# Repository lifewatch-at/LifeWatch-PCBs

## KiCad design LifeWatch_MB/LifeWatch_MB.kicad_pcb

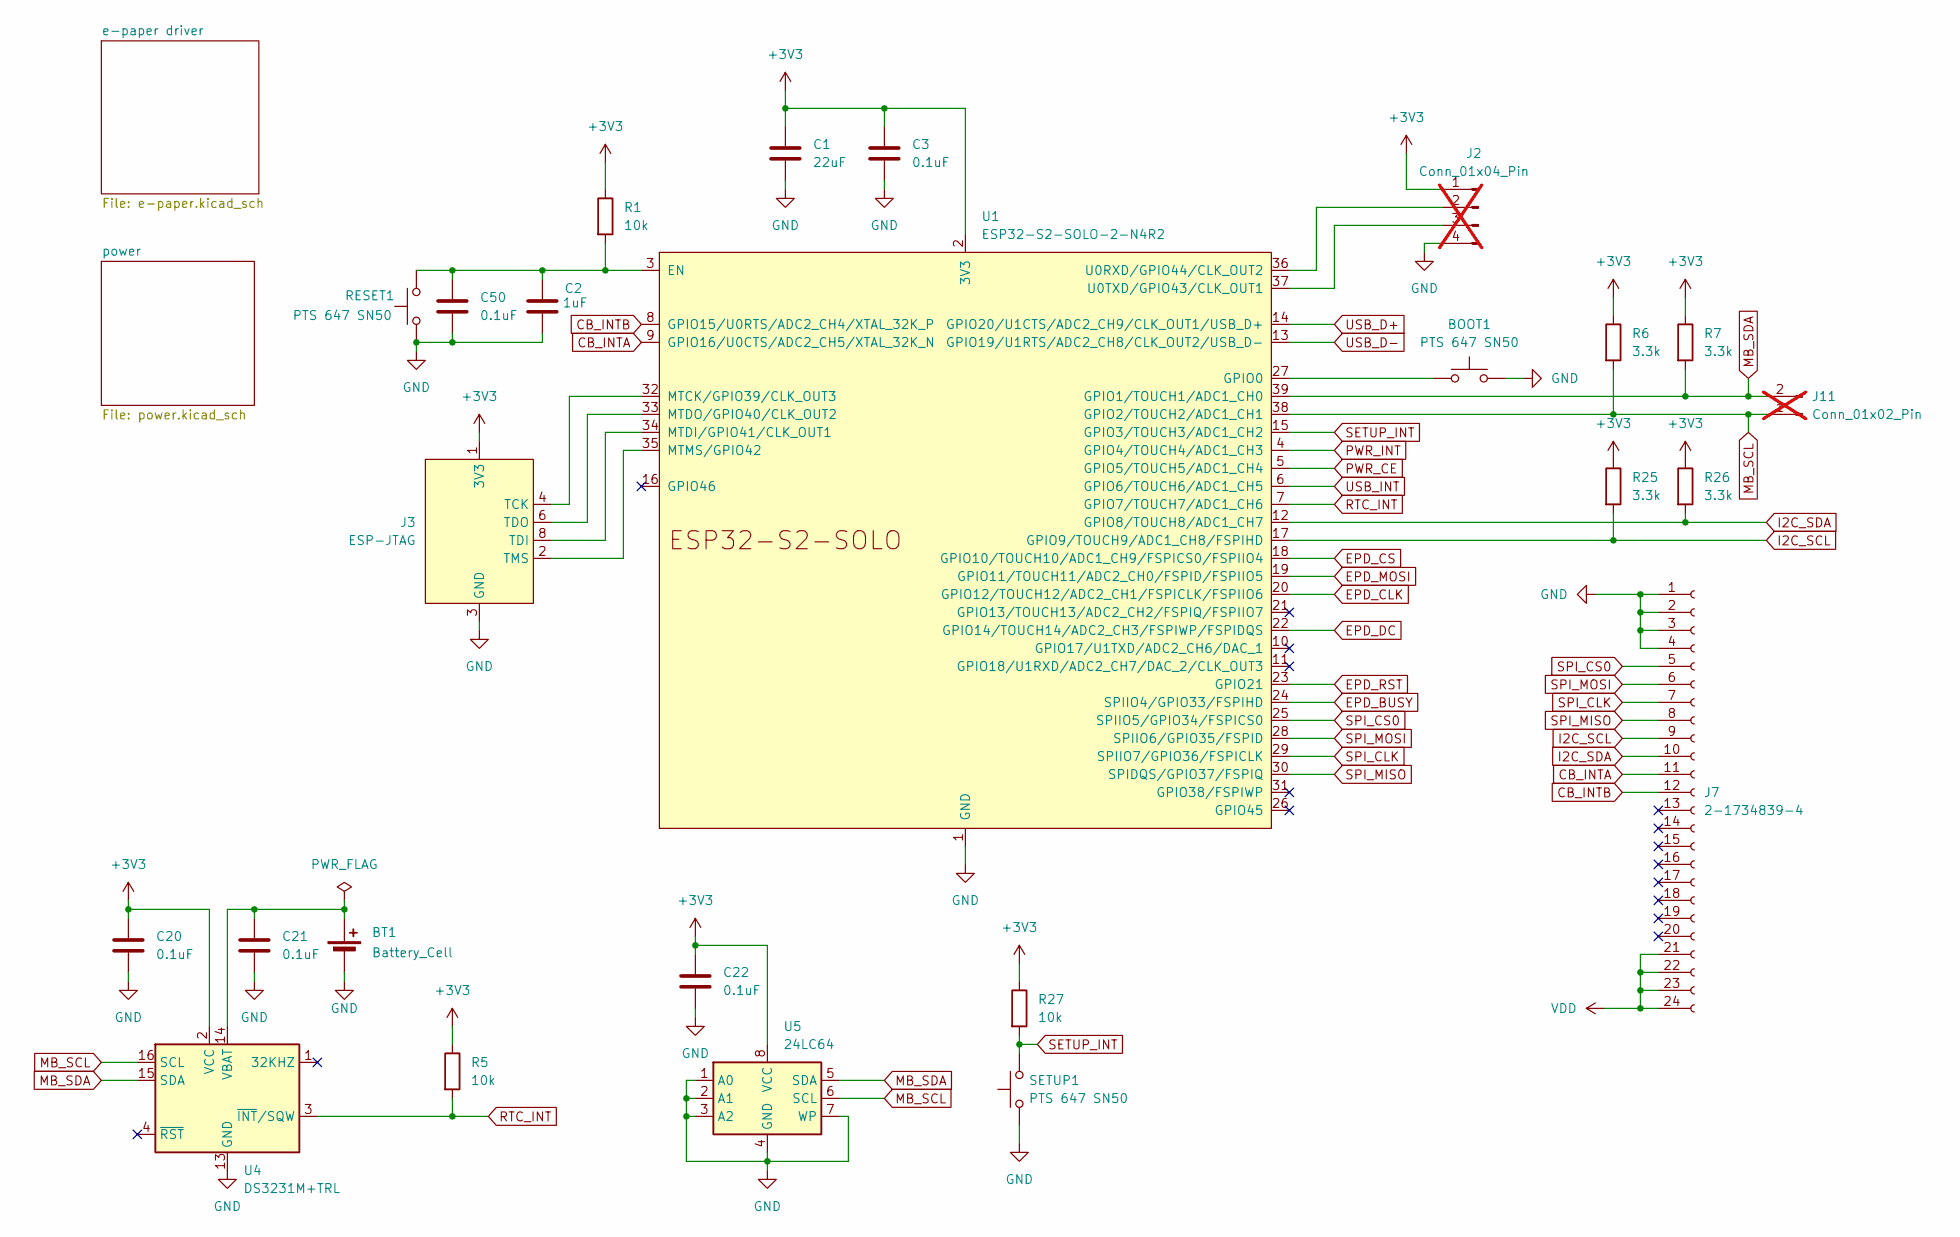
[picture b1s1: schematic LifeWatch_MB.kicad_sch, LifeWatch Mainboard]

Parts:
BOOT1: PTS 647 SN50; SW_SPST_PTS647_Sx50; Manufacturer_Part_Number PTS 647 SN50 SMTR2 LFS
BT1: Battery_Cell; BatteryHolder_Keystone_1060_1x2032; Manufacturer_Part_Number Keystone 3034
C1: 22uF; C_0805_2012Metric; Manufacturer_Part_Number CL21A226MQQNNNE
C2: 1uF; C_0603_1608Metric; Manufacturer_Part_Number CC0603KRX7R7BB105
C3, C20, C21, C22, C50: 0.1uF; C_0402_1005Metric; Manufacturer_Part_Number CL05B104KP5NNNC
J2: Conn_01x04_Pin; PinHeader_1x04_P2.54mm_Vertical; not fitted
J3: ESP-JTAG; IDC-Header_2x05_P2.54mm_Vertical
J7: 2-1734839-4; TE_2-1734839-4_1x24-1MP_P0.5mm_Horizontal; Manufacturer_Part_Number 2-1734839-4
J11: Conn_01x02_Pin; PinHeader_1x02_P2.54mm_Vertical; not fitted
R1, R5, R27: 10k; R_0805_2012Metric; Manufacturer_Part_Number RC0805FR-0710KL
R6, R7, R25, R26: 3.3k; R_0805_2012Metric; Manufacturer_Part_Number RC0805FR-073K3L
RESET1: PTS 647 SN50; SW_SPST_PTS647_Sx50; Manufacturer_Part_Number PTS 647 SN50 SMTR2 LFS
SETUP1: PTS 647 SN50; SW_SPST_PTS647_Sx50; Manufacturer_Part_Number PTS 647 SN50 SMTR2 LFS
U1: ESP32-S2-SOLO-2-N4R2; ESP32-S2-SOLO; Manufacturer_Part_Number ESP32-S2-SOLO-2-N4R2
U4: DS3231M+TRL; SOIC-16W_7.5x10.3mm_P1.27mm; Manufacturer_Part_Number DS3231M+TRL
U5: 24LC64; SOIC-8_3.9x4.9mm_P1.27mm; Manufacturer_Part_Number 24LC64T-I/SN

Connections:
+3V3: C1.1, C3.1, C20.1, C22.1, J2.1, J3.1 (3V3), R1.1, R5.1, R6.1, R7.1, R25.1, R26.1, R27.1, U1.2 (3V3), U4.2 (VCC), U5.8 (VCC); also elsewhere on the board
CB_INTA: J7.11, U1.9 (GPIO16/U0CTS/ADC2_CH5/XTAL_32K_N)
CB_INTB: J7.12, U1.8 (GPIO15/U0RTS/ADC2_CH4/XTAL_32K_P)
EPD_BUSY: U1.24 (SPIIO4/GPIO33/FSPIHD); also elsewhere on the board
EPD_CLK: U1.20 (GPIO12/TOUCH12/ADC2_CH1/FSPICLK/FSPIIO6); also elsewhere on the board
EPD_CS: U1.18 (GPIO10/TOUCH10/ADC1_CH9/FSPICS0/FSPIIO4); also elsewhere on the board
EPD_DC: U1.22 (GPIO14/TOUCH14/ADC2_CH3/FSPIWP/FSPIDQS); also elsewhere on the board
EPD_MOSI: U1.19 (GPIO11/TOUCH11/ADC2_CH0/FSPID/FSPIIO5); also elsewhere on the board
EPD_RST: U1.23 (GPIO21); also elsewhere on the board
GND: BOOT1.2, BT1.2 (-), C1.2, C2.2, C3.2, C20.2, C21.2, C22.2, C50.2, J2.4, J3.3 (GND), J3.5 (GND), J3.7 (GND), J3.9 (GND), J7.1, J7.2, J7.3, J7.4, RESET1.1, SETUP1.1, U1.1 (GND), U1.40 (GND), U1.41 (GND), U4.5 (GND), U4.6 (GND), U4.7 (GND), U4.8 (GND), U4.9 (GND), U4.10 (GND), U4.11 (GND), U4.12 (GND), U4.13 (GND), U5.1 (A0), U5.2 (A1), U5.3 (A2), U5.4 (GND), U5.7 (WP); also elsewhere on the board
I2C_SCL: J7.9, R25.2, U1.17 (GPIO9/TOUCH9/ADC1_CH8/FSPIHD)
I2C_SDA: J7.10, R26.2, U1.12 (GPIO8/TOUCH8/ADC1_CH7)
MB_SCL: J11.1, R6.2, U1.38 (GPIO2/TOUCH2/ADC1_CH1), U4.16 (SCL), U5.6 (SCL); also elsewhere on the board
MB_SDA: J11.2, R7.2, U1.39 (GPIO1/TOUCH1/ADC1_CH0), U4.15 (SDA), U5.5 (SDA); also elsewhere on the board
unnamed: BT1.1 (+), C21.1, U4.14 (VBAT)
unnamed: J2.2, U1.36 (U0RXD/GPIO44/CLK_OUT2)
unnamed: J2.3, U1.37 (U0TXD/GPIO43/CLK_OUT1)
unnamed: J3.4 (TCK), U1.32 (MTCK/GPIO39/CLK_OUT3)
unnamed: J3.8 (TDI), U1.34 (MTDI/GPIO41/CLK_OUT1)
unnamed: J3.6 (TDO), U1.33 (MTDO/GPIO40/CLK_OUT2)
unnamed: J3.2 (TMS), U1.35 (MTMS/GPIO42)
unnamed: C2.1, C50.1, R1.2, RESET1.2, U1.3 (EN)
unnamed: BOOT1.1, U1.27 (GPIO0)
PWR_CE: U1.5 (GPIO5/TOUCH5/ADC1_CH4); also elsewhere on the board
PWR_INT: U1.4 (GPIO4/TOUCH4/ADC1_CH3); also elsewhere on the board
RTC_INT: R5.2, U1.7 (GPIO7/TOUCH7/ADC1_CH6), U4.3 (~INT/SQW)
SETUP_INT: R27.2, SETUP1.2, U1.15 (GPIO3/TOUCH3/ADC1_CH2)
SPI_CLK: J7.7, U1.29 (SPIIO7/GPIO36/FSPICLK)
SPI_CS0: J7.5, U1.25 (SPIIO5/GPIO34/FSPICS0)
SPI_MISO: J7.8, U1.30 (SPIDQS/GPIO37/FSPIQ)
SPI_MOSI: J7.6, U1.28 (SPIIO6/GPIO35/FSPID)
USB_D+: U1.14 (GPIO20/U1CTS/ADC2_CH9/CLK_OUT1/USB_D+); also elsewhere on the board
USB_D-: U1.13 (GPIO19/U1RTS/ADC2_CH8/CLK_OUT2/USB_D-); also elsewhere on the board
USB_INT: U1.6 (GPIO6/TOUCH6/ADC1_CH5); also elsewhere on the board
VDD: J7.21, J7.22, J7.23, J7.24; also elsewhere on the board

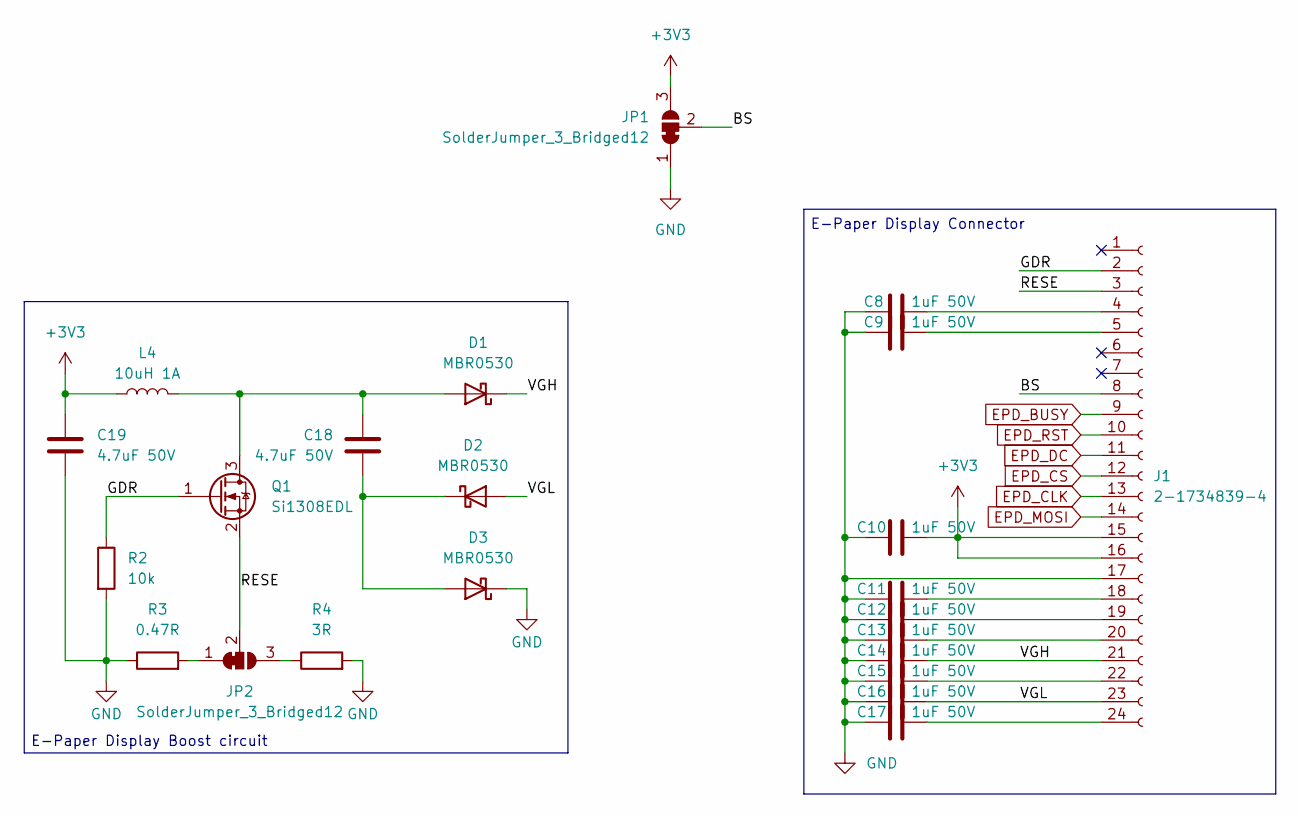
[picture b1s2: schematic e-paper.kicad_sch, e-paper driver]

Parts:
C8, C9, C10, C11, C12, C13, C14, C15, C16, C17: 1uF 50V; C_0805_2012Metric; Manufacturer_Part_Number CL21B105KBFNNNE
C18, C19: 4.7uF 50V; C_0805_2012Metric; Manufacturer_Part_Number GRM21BR61H475KE51L
D1, D2, D3: MBR0530; D_SOD-123; Manufacturer_Part_Number MBR0530T1G
J1: 2-1734839-4; TE_2-1734839-4_1x24-1MP_P0.5mm_Horizontal; Manufacturer_Part_Number 2-1734839-4
JP1, JP2: SolderJumper_3_Bridged12; SolderJumper-3_P1.3mm_Bridged12_RoundedPad1.0x1.5mm
L4: 10uH 1A; L_Vishay_IHLP-2525; Manufacturer_Part_Number IHLP2525CZER100M01
Q1: Si1308EDL; SOT-323_SC-70; Manufacturer_Part_Number SI1308EDL-T1-GE3
R2: 10k; R_0805_2012Metric; Manufacturer_Part_Number RC0805FR-0710KL
R3: 0.47R; R_0805_2012Metric; Manufacturer_Part_Number ERJ-6RQFR47V
R4: 3R; R_0805_2012Metric; Manufacturer_Part_Number RC0805FR-073RL

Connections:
+3V3: C10.2, C19.1, J1.15, J1.16, JP1.3 (B), L4.1; also elsewhere on the board
/e-paper driver/BS: J1.8, JP1.2 (C)
/e-paper driver/GDR: J1.2, Q1.1 (G), R2.1
/e-paper driver/RESE: J1.3, JP2.2 (C), Q1.2 (S)
/e-paper driver/VGH: C14.2, D1.1 (K), J1.21
/e-paper driver/VGL: C16.2, D2.2 (A), J1.23
EPD_BUSY: J1.9; also elsewhere on the board
EPD_CLK: J1.13; also elsewhere on the board
EPD_CS: J1.12; also elsewhere on the board
EPD_DC: J1.11; also elsewhere on the board
EPD_MOSI: J1.14; also elsewhere on the board
EPD_RST: J1.10; also elsewhere on the board
GND: C8.1, C9.1, C10.1, C11.1, C12.1, C13.1, C14.1, C15.1, C16.1, C17.1, C19.2, D3.1 (K), J1.17, JP1.1 (A), R2.2, R3.1, R4.2; also elsewhere on the board
unnamed: C18.1, D1.2 (A), L4.2, Q1.3 (D)
unnamed: C18.2, D2.1 (K), D3.2 (A)
unnamed: C8.2, J1.4
unnamed: C9.2, J1.5
unnamed: C11.2, J1.18
unnamed: C12.2, J1.19
unnamed: C13.2, J1.20
unnamed: C15.2, J1.22
unnamed: C17.2, J1.24
unnamed: JP2.1 (A), R3.2
unnamed: JP2.3 (B), R4.1

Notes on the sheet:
E-Paper Display Connector
E-Paper Display Boost circuit

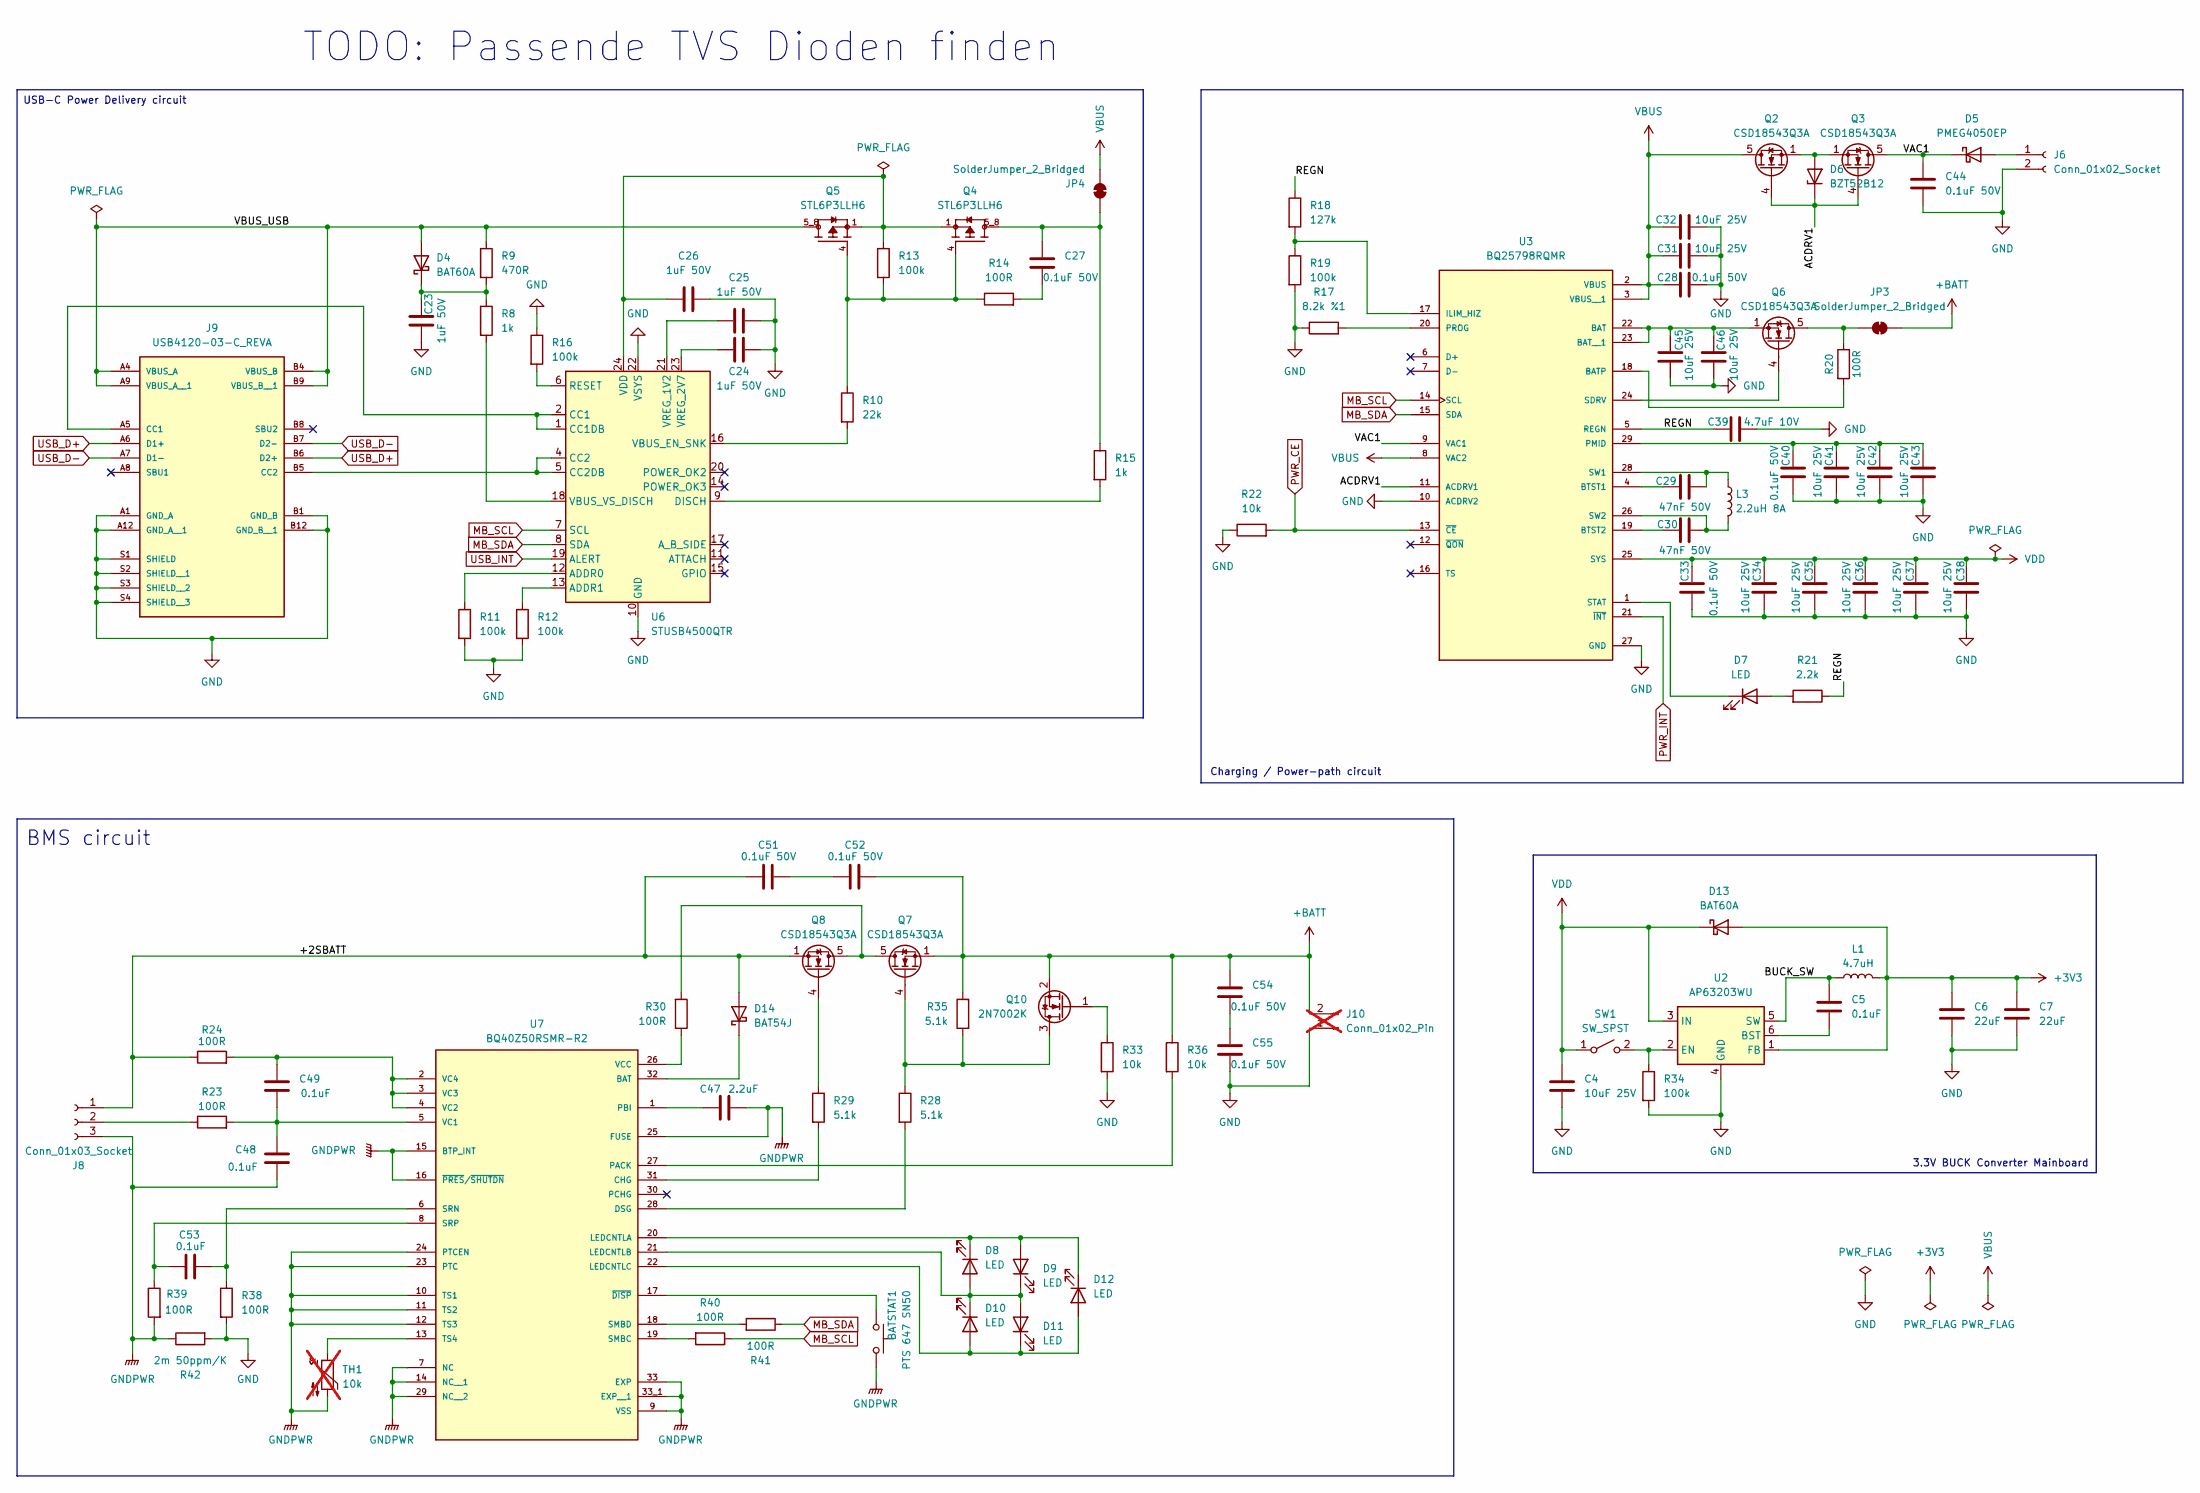
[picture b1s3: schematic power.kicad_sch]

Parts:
BATSTAT1: PTS 647 SN50; SW_SPST_PTS647_Sx50; Manufacturer_Part_Number PTS 647 SN50 SMTR2 LFS
C4, C31, C32, C34, C35, C36, C37, C38, C41, C42, C43, C45, C46: 10uF 25V; C_0805_2012Metric; Manufacturer_Part_Number GRM21BR61E106KA73L
C5, C48, C49, C53: 0.1uF; C_0402_1005Metric; Manufacturer_Part_Number CL05B104KP5NNNC
C6, C7: 22uF; C_0805_2012Metric; Manufacturer_Part_Number CL21A226MQQNNNE
C23, C24, C25, C26: 1uF 50V; C_0805_2012Metric; Manufacturer_Part_Number CL21B105KBFNNNE
C27, C28, C33, C40, C44, C51, C52, C54, C55: 0.1uF 50V; C_0402_1005Metric; Manufacturer_Part_Number GRM155R71H104KE14D
C29, C30: 47nF 50V; C_0402_1005Metric; Manufacturer_Part_Number CGA2B3X7R1H473K050BB
C39: 4.7uF 10V; C_0603_1608Metric; Manufacturer_Part_Number CL10A475KP8NNNC
C47: 2.2uF; C_0603_1608Metric; Manufacturer_Part_Number GRM188R71A225KE15D
D4, D13: BAT60A; D_SOD-323; Manufacturer_Part_Number BAT60AE6327HTSA1
D5: PMEG4050EP; D_SOD-128; Manufacturer_Part_Number PMEG4050EP,115
D6: BZT52B12; D_SOD-123F; Manufacturer_Part_Number BZT52C12-7-F
D7: LED; LED_D3.0mm; Manufacturer_Part_Number 150060RS75000
D8, D9, D10, D11, D12: LED; LED_0603_1608Metric; Manufacturer_Part_Number 150060RS75000
D14: BAT54J; D_SOD-323F; Manufacturer_Part_Number BAT54J,115
J6: Conn_01x02_Socket; PhoenixContact_MCV_1,5_2-GF-3.5_1x02_P3.50mm_Vertical_Threa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; Manufacturer_Part_Number 1843224
J8: Conn_01x03_Socket; JST_XH_B3B-XH-A_1x03_P2.50mm_Vertical; Manufacturer_Part_Number B3B-XH-A
J9: USB4120-03-C_REVA; GCT_USB4120-03-C_REVA; PARTREV A
J10: Conn_01x02_Pin; PinHeader_1x02_P2.54mm_Vertical; not fitted
JP3, JP4: SolderJumper_2_Bridged; SolderJumper-2_P1.3mm_Bridged_RoundedPad1.0x1.5mm
L1: 4.7uH; L_Vishay_IHLP-2525; Manufacturer_Part_Number IHLP2525CZER4R7M01
L3: 2.2uH 8A; L_Vishay_IHLP-2525; Manufacturer_Part_Number IHLP2525CZER2R2M01
Q2, Q3, Q6, Q7, Q8: CSD18543Q3A; VSON-8_3.3x3.3mm_P0.65mm_NexFET; Manufacturer_Part_Number CSD18543Q3A
Q4, Q5: STL6P3LLH6; TRANS_STL6P3LLH6; PARTREV 4
Q10: 2N7002K; SOT-23; Manufacturer_Part_Number 2N7002K
R8, R15: 1k; R_0805_2012Metric; Manufacturer_Part_Number RC0805FR-071KL
R9: 470R; R_0805_2012Metric; Manufacturer_Part_Number RC0805FR-07470RL
R10: 22k; R_0805_2012Metric; Manufacturer_Part_Number RC0805FR-0722KL
R11, R12, R13, R16, R19, R34: 100k; R_0805_2012Metric; Manufacturer_Part_Number RC0805FR-07100KL
R14, R20, R23, R24, R30, R38, R39, R40, R41: 100R; R_0805_2012Metric; Manufacturer_Part_Number RC0805FR-07100RL
R17: 8.2k %1; R_0805_2012Metric; Manufacturer_Part_Number RC0805FR-078K2L
R18: 127k; R_0805_2012Metric; Manufacturer_Part_Number RC0805FR-07127KL
R21: 2.2k; R_0805_2012Metric; Manufacturer_Part_Number RC0805FR-072K2L
R22, R33, R36: 10k; R_0805_2012Metric; Manufacturer_Part_Number RC0805FR-0710KL
R28, R29, R35: 5.1k; R_0805_2012Metric; Manufacturer_Part_Number RC0805FR-075K1L
R42: 2m 50ppm/K; R_2512_6332Metric_Pad1.40x3.35mm_HandSolder; Manufacturer_Part_Number BVT-I-R002-1.0
SW1: SW_SPST; PinHeader_1x02_P2.54mm_Horizontal
TH1: 10k; PinHeader_1x02_P2.54mm_Vertical; not fitted
U2: AP63203WU; TSOT-23-6; Manufacturer_Part_Number AP63203WU-7
U3: BQ25798RQMR; QFN40P400X400X100-29N; PARTREV 11/2019
U6: STUSB4500QTR; QFN-24-1EP_4x4mm_P0.5mm_EP2.7x2.7mm; Manufacturer_Part_Number STUSB4500QTR
U7: BQ40Z50RSMR-R2; QFN40P400X400X100-33N; PARTREV B

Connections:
+3V3: C6.1, C7.1, D13.2 (A), L1.2, U2.1 (FB); also elsewhere on the board
+BATT: C52.2, C54.1, J10.2, JP3.2 (B), Q7.1 (S), Q7.2 (S), Q7.3 (S), Q10.2 (S), R35.1, R36.1
/power/+2SBATT: C51.1, D14.2 (A), J8.1, Q8.1 (S), Q8.2 (S), Q8.3 (S), R24.1
/power/ACDRV1: D6.1 (K), Q2.4 (G), Q3.4 (G), U3.11 (ACDRV1)
/power/BUCK_SW: C5.2, L1.1, U2.5 (SW)
/power/REGN: C39.1, R18.1, R21.1, U3.5 (REGN)
/power/VAC1: C44.1, D5.1 (K), Q3.5 (D), U3.9 (VAC1)
/power/VBUS_USB: D4.2 (A), J9.A4 (VBUS_A), J9.A9 (VBUS_A__1), J9.B4 (VBUS_B), J9.B9 (VBUS_B__1), Q5.5_8, R9.1
GND: C4.2, C6.2, C7.2, C23.2, C24.2, C25.2, C26.2, C28.2, C31.2, C32.2, C33.2, C34.2, C35.2, C36.2, C37.2, C38.2, C39.2, C40.2, C41.2, C42.2, C43.2, C44.2, C45.2, C46.2, C55.2, J6.2, J9.A1 (GND_A), J9.A12 (GND_A__1), J9.B1 (GND_B), J9.B12 (GND_B__1), J9.S1 (SHIELD), J9.S2 (SHIELD__1), J9.S3 (SHIELD__2), J9.S4 (SHIELD__3), J10.1, R11.2, R12.2, R16.1, R17.1, R19.2, R22.1, R33.2, R34.2, R38.2, R42.2, U2.4 (GND), U3.10 (ACDRV2), U3.27 (GND), U6.10 (GND), U6.22 (VSYS), U6.25 (GND); also elsewhere on the board
GNDPWR: BATSTAT1.2, C47.2, C48.2, J8.3, R39.2, R42.1, TH1.2, U7.7 (NC), U7.9 (VSS), U7.10 (TS1), U7.11 (TS2), U7.12 (TS3), U7.14 (NC__1), U7.15 (BTP_INT), U7.16 (~PRES/~SHUTDN), U7.23 (PTC), U7.24 (PTCEN), U7.25 (FUSE), U7.29 (NC__2), U7.33 (EXP), U7.33_1 (EXP__1)
MB_SCL: R40.1, U3.14 (SCL), U6.7 (SCL); also elsewhere on the board
MB_SDA: R41.1, U3.15 (SDA), U6.8 (SDA); also elsewhere on the board
unnamed: C27.2, R14.2
unnamed: C51.2, C52.1
unnamed: C54.2, C55.1
unnamed: C23.1, D4.1 (K), R8.1, R9.2
unnamed: D5.2 (A), J6.1
unnamed: D6.2 (A), Q2.1 (S), Q2.2 (S), Q2.3 (S), Q3.1 (S), Q3.2 (S), Q3.3 (S)
unnamed: D7.2 (A), R21.2
unnamed: D7.1 (K), U3.1 (STAT)
unnamed: D10.2 (A), D11.1 (K), D12.2 (A), U7.22 (LEDCNTLC)
unnamed: D8.2 (A), D9.1 (K), D10.1 (K), D11.2 (A), U7.21 (LEDCNTLB)
unnamed: D8.1 (K), D9.2 (A), D12.1 (K), U7.20 (LEDCNTLA)
unnamed: D14.1 (K), U7.32 (BAT)
unnamed: J8.2, R23.1
unnamed: J9.A5 (CC1), U6.1 (CC1DB), U6.2 (CC1)
unnamed: J9.B5 (CC2), U6.4 (CC2), U6.5 (CC2DB)
unnamed: JP3.1 (A), Q6.5 (D), R20.1
unnamed: C27.1, JP4.1 (A), Q4.5_8, R15.1
unnamed: Q4.4, Q5.4, R10.1, R13.2, R14.1
unnamed: Q6.4 (G), U3.24 (SDRV)
unnamed: Q7.5 (D), Q8.5 (D), R30.2
unnamed: Q8.4 (G), R29.1
unnamed: Q7.4 (G), Q10.3 (D), R28.1, R35.2
unnamed: Q10.1 (G), R33.1
unnamed: R34.1, SW1.2 (B), U2.2 (EN)
unnamed: C5.1, U2.6 (BST)
unnamed: C45.1, C46.1, Q6.1 (S), Q6.2 (S), Q6.3 (S), U3.22 (BAT), U3.23 (BAT__1)
unnamed: R20.2, U3.18 (BATP)
unnamed: C29.1, U3.4 (BTST1)
unnamed: C30.1, U3.19 (BTST2)
unnamed: R18.2, R19.1, U3.17 (ILIM_HIZ)
unnamed: C40.1, C41.1, C42.1, C43.1, U3.29 (PMID)
unnamed: R17.2, U3.20 (PROG)
unnamed: C29.2, L3.1, U3.28 (SW1)
unnamed: C30.2, L3.2, U3.26 (SW2)
unnamed: R11.1, U6.12 (ADDR0)
unnamed: R12.1, U6.13 (ADDR1)
unnamed: R15.2, U6.9 (DISCH)
unnamed: R16.2, U6.6 (RESET)
unnamed: R10.2, U6.16 (VBUS_EN_SNK)
unnamed: R8.2, U6.18 (VBUS_VS_DISCH)
unnamed: C26.1, Q4.1, Q4.2, Q4.3, Q5.1, Q5.2, Q5.3, R13.1, U6.24 (VDD)
unnamed: C25.1, U6.21 (VREG_1V2)
unnamed: C24.1, U6.23 (VREG_2V7)
unnamed: R29.2, U7.31 (CHG)
unnamed: R28.2, U7.28 (DSG)
unnamed: R36.2, U7.27 (PACK)
unnamed: C47.1, U7.1 (PBI)
unnamed: R40.2, U7.19 (SMBC)
unnamed: R41.2, U7.18 (SMBD)
unnamed: C53.2, R38.1, U7.6 (SRN)
unnamed: C53.1, R39.1, U7.8 (SRP)
unnamed: TH1.1, U7.13 (TS4)
unnamed: C48.1, C49.2, R23.2, U7.5 (VC1)
unnamed: C49.1, R24.2, U7.2 (VC4), U7.3 (VC3), U7.4 (VC2)
unnamed: R30.1, U7.26 (VCC)
unnamed: BATSTAT1.1, U7.17 (~DISP)
PWR_CE: R22.2, U3.13 (~CE); also elsewhere on the board
PWR_INT: U3.21 (~INT); also elsewhere on the board
USB_D+: J9.A6 (D1+), J9.B6 (D2+); also elsewhere on the board
USB_D-: J9.A7 (D1-), J9.B7 (D2-); also elsewhere on the board
USB_INT: U6.19 (ALERT); also elsewhere on the board
VBUS: C28.1, C31.1, C32.1, JP4.2 (B), Q2.5 (D), U3.2 (VBUS), U3.3 (VBUS__1), U3.8 (VAC2)
VDD: C4.1, C33.1, C34.1, C35.1, C36.1, C37.1, C38.1, D13.1 (K), SW1.1 (A), U2.3 (IN), U3.25 (SYS); also elsewhere on the board

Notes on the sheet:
TODO: Passende TVS Dioden finden
USB-C Power Delivery circuit
3.3V BUCK Converter Mainboard
BMS circuit
Charging / Power-path circuit

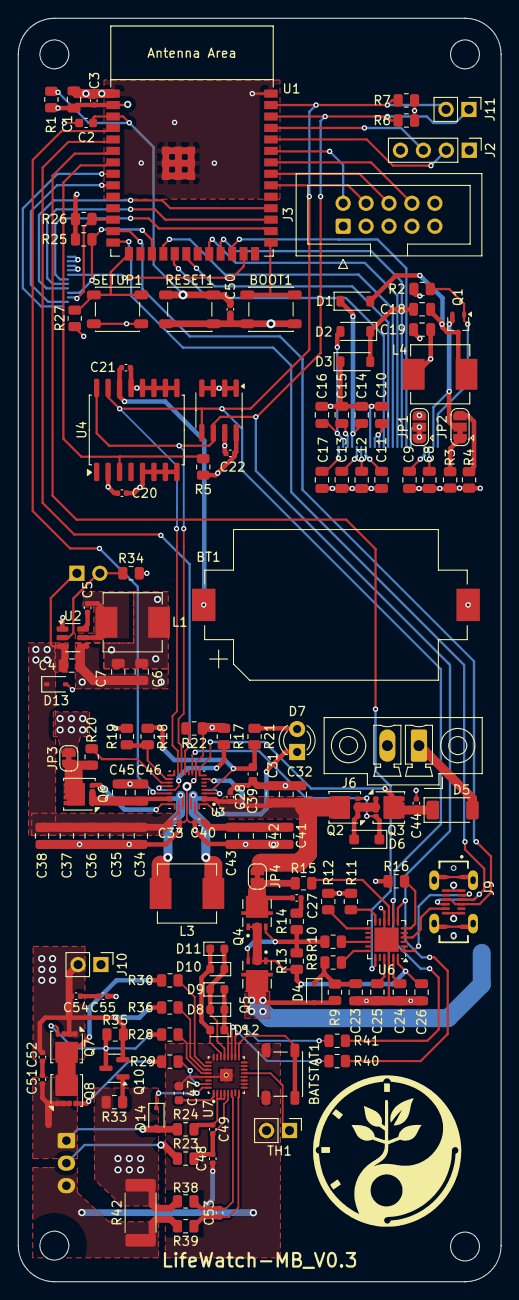
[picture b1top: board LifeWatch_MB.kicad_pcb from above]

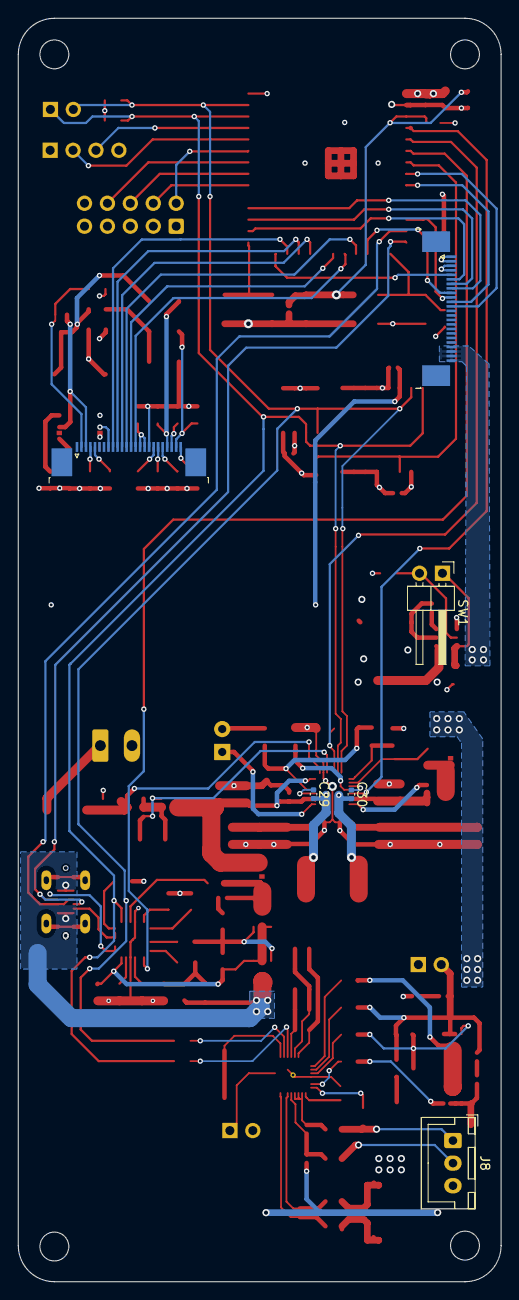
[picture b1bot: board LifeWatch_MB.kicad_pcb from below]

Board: 4 copper layers, 53.5 x 140.0 mm, 147 parts (6 on the bottom side), 116 nets.

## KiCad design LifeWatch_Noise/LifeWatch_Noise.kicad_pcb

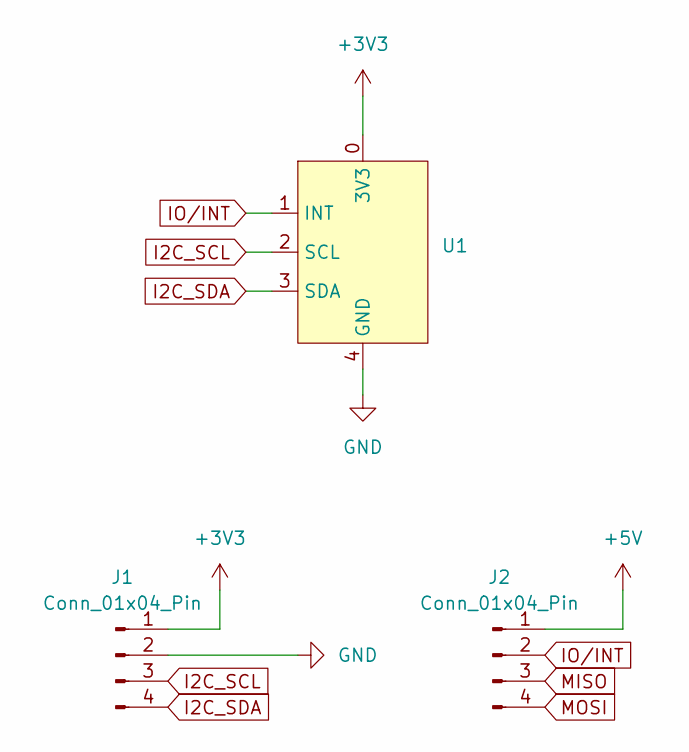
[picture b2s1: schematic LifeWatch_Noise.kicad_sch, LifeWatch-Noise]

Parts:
J1, J2: Conn_01x04_Pin; PinHeader_1x04_P2.54mm_Vertical
U1: i2c_decibel

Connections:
+3V3: J1.1, U1.0 (3V3)
+5V: J2.1
GND: J1.2, U1.4 (GND)
I2C_SCL: J1.3, U1.2 (SCL)
I2C_SDA: J1.4, U1.3 (SDA)
IO/INT: J2.2, U1.1 (INT)
MISO: J2.3
MOSI: J2.4

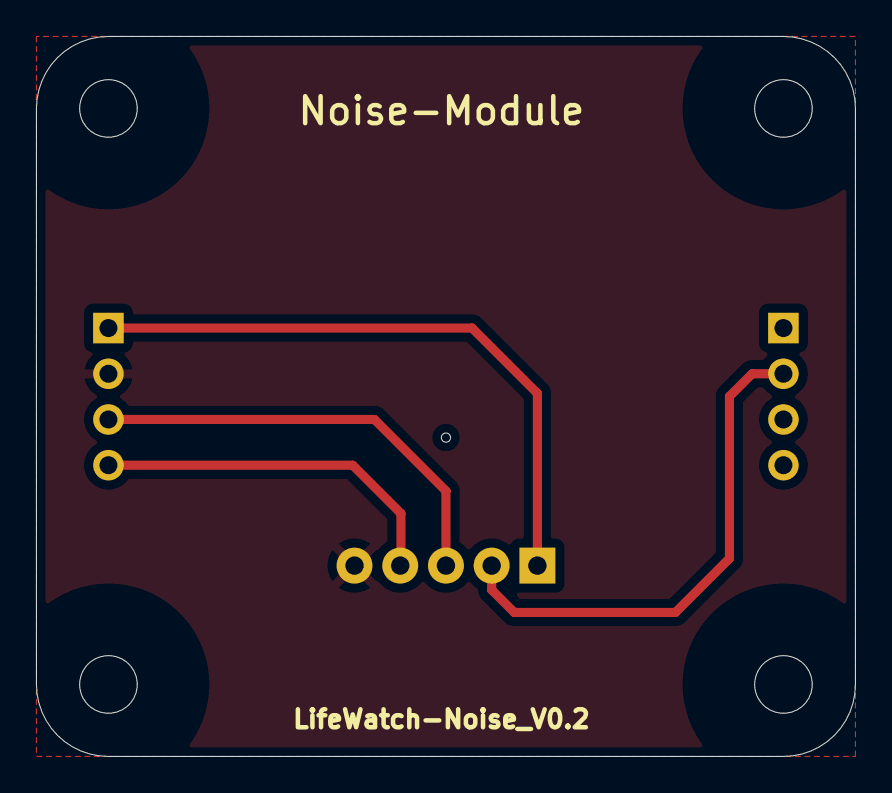
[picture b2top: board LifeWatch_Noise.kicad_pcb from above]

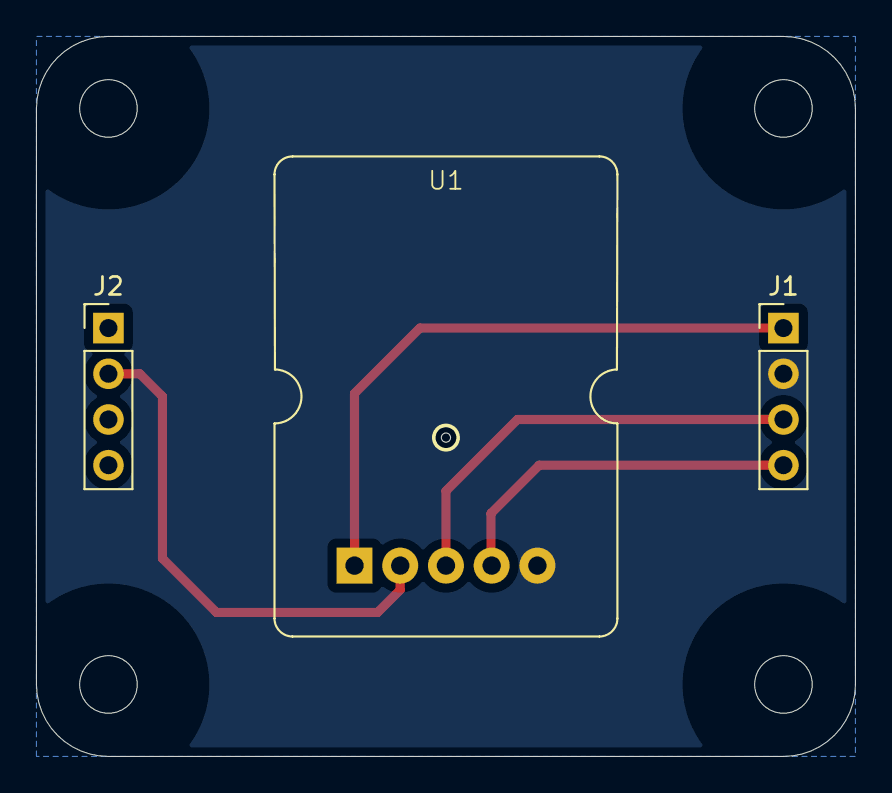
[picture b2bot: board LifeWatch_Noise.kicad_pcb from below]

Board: 2 copper layers, 45.5 x 40.0 mm, 3 parts (3 on the bottom side), 5 nets.

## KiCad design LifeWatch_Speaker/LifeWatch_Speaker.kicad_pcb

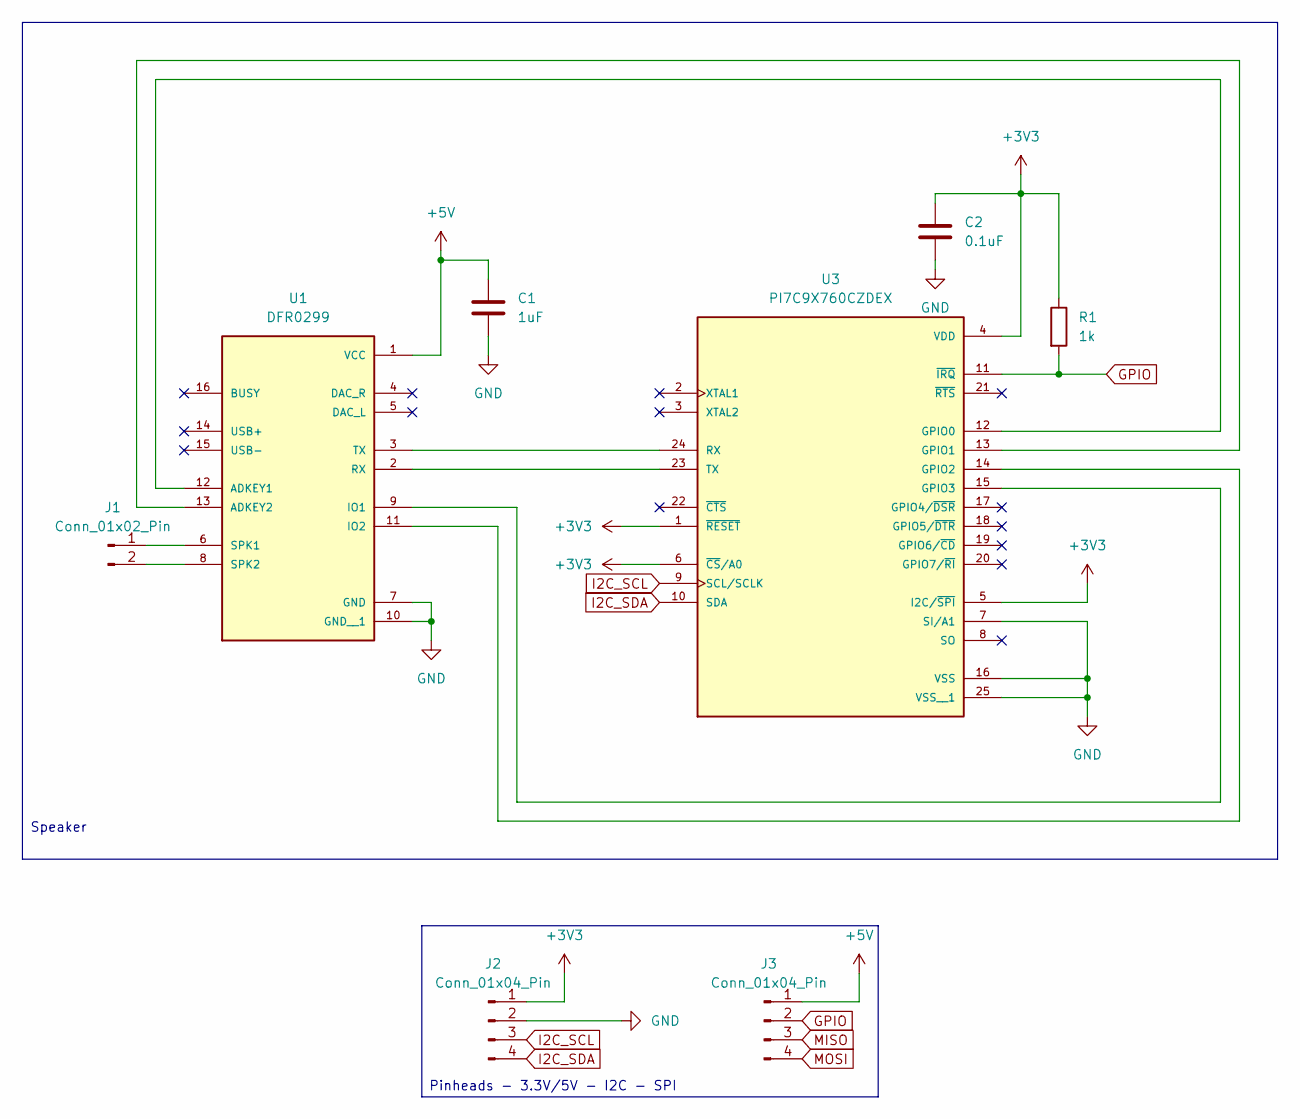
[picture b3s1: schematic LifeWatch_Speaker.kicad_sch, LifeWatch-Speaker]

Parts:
C1: 1uF; C_0603_1608Metric; Manufacturer_Part_Number CC0603KRX7R7BB105
C2: 0.1uF; C_0402_1005Metric; Manufacturer_Part_Number CL05B104KP5NNNC
J1: Conn_01x02_Pin; PinHeader_1x02_P2.54mm_Vertical
J2, J3: Conn_01x04_Pin; PinHeader_1x04_P2.54mm_Vertical
R1: 1k; R_0805_2012Metric; Manufacturer_Part_Number RC0805FR-071KL
U1: DFR0299; MODULE_DFR0299; Manufacturer_Part_Number DFR0299
U3: PI7C9X760CZDEX; QFN50P400X400X90-25N; PARTREV Rev 6-2

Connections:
+3V3: C2.1, J2.1, R1.1, U3.1 (~RESET), U3.4 (VDD), U3.5 (I2C/~SPI), U3.6 (~CS/A0)
+5V: C1.1, J3.1, U1.1 (VCC)
GND: C1.2, C2.2, J2.2, U1.7 (GND), U1.10 (GND__1), U3.7 (SI/A1), U3.16 (VSS), U3.25 (VSS__1)
I2C_SCL: J2.3, U3.9 (SCL/SCLK)
I2C_SDA: J2.4, U3.10 (SDA)
IO/INT: J3.2, R1.2, U3.11 (~IRQ)
MISO: J3.3
MOSI: J3.4
unnamed: J1.1, U1.6 (SPK1)
unnamed: J1.2, U1.8 (SPK2)
unnamed: U1.12 (ADKEY1), U3.12 (GPIO0)
unnamed: U1.13 (ADKEY2), U3.13 (GPIO1)
unnamed: U1.9 (IO1), U3.15 (GPIO3)
unnamed: U1.11 (IO2), U3.14 (GPIO2)
unnamed: U1.2 (RX), U3.23 (TX)
unnamed: U1.3 (TX), U3.24 (RX)

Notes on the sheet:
Pinheads - 3.3V/5V - I2C - SPI
Speaker

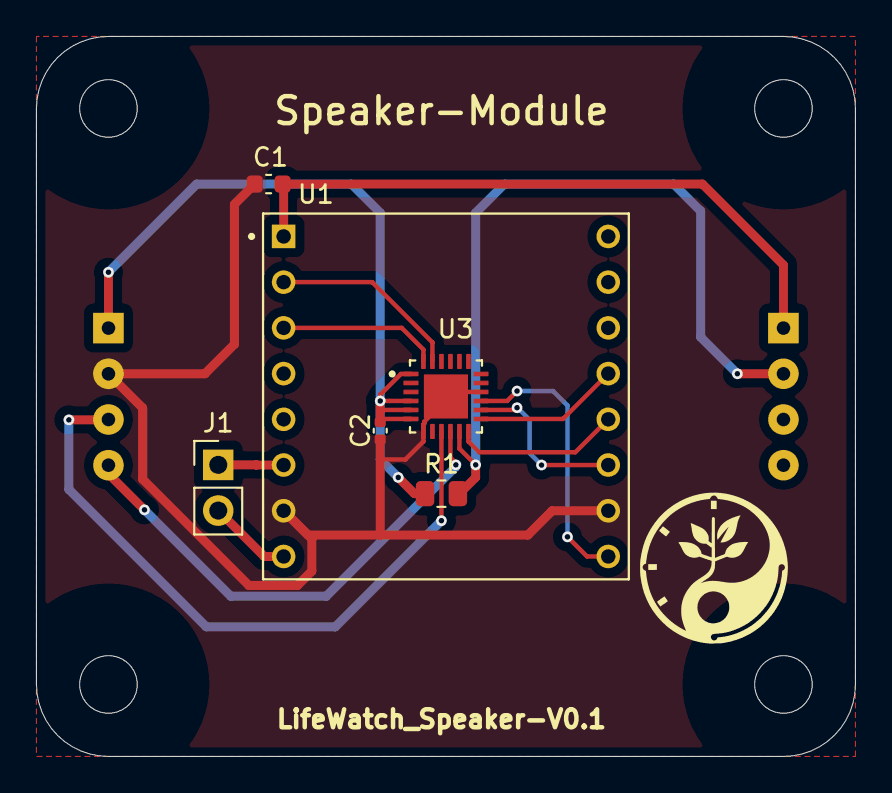
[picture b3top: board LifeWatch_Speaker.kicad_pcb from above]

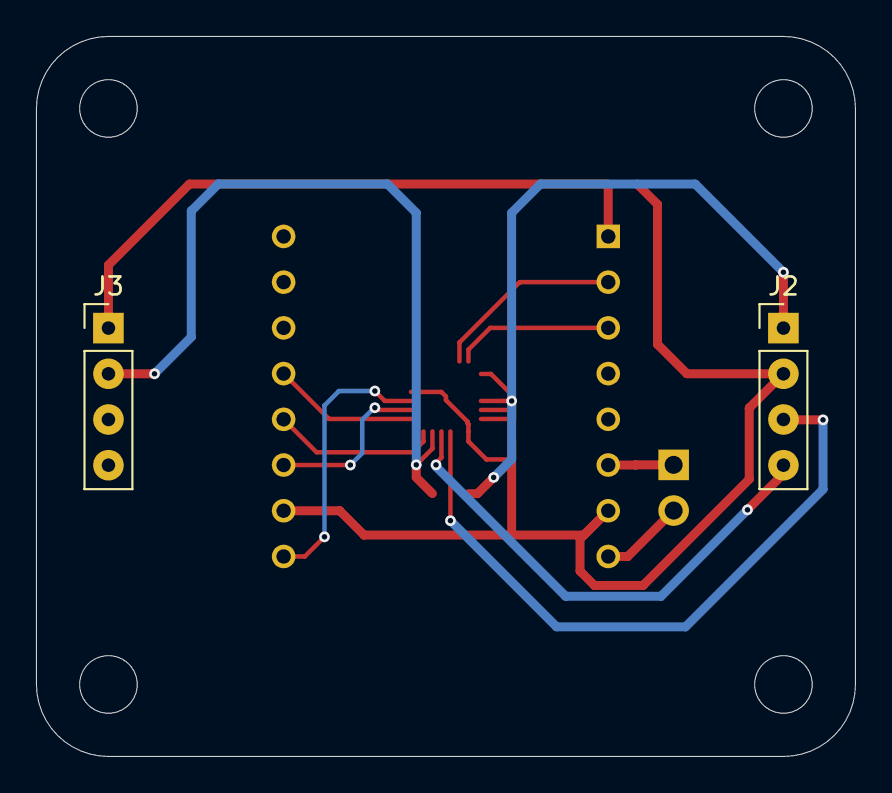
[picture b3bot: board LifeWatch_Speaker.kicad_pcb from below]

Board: 2 copper layers, 45.5 x 40.0 mm, 8 parts (2 on the bottom side), 14 nets.
